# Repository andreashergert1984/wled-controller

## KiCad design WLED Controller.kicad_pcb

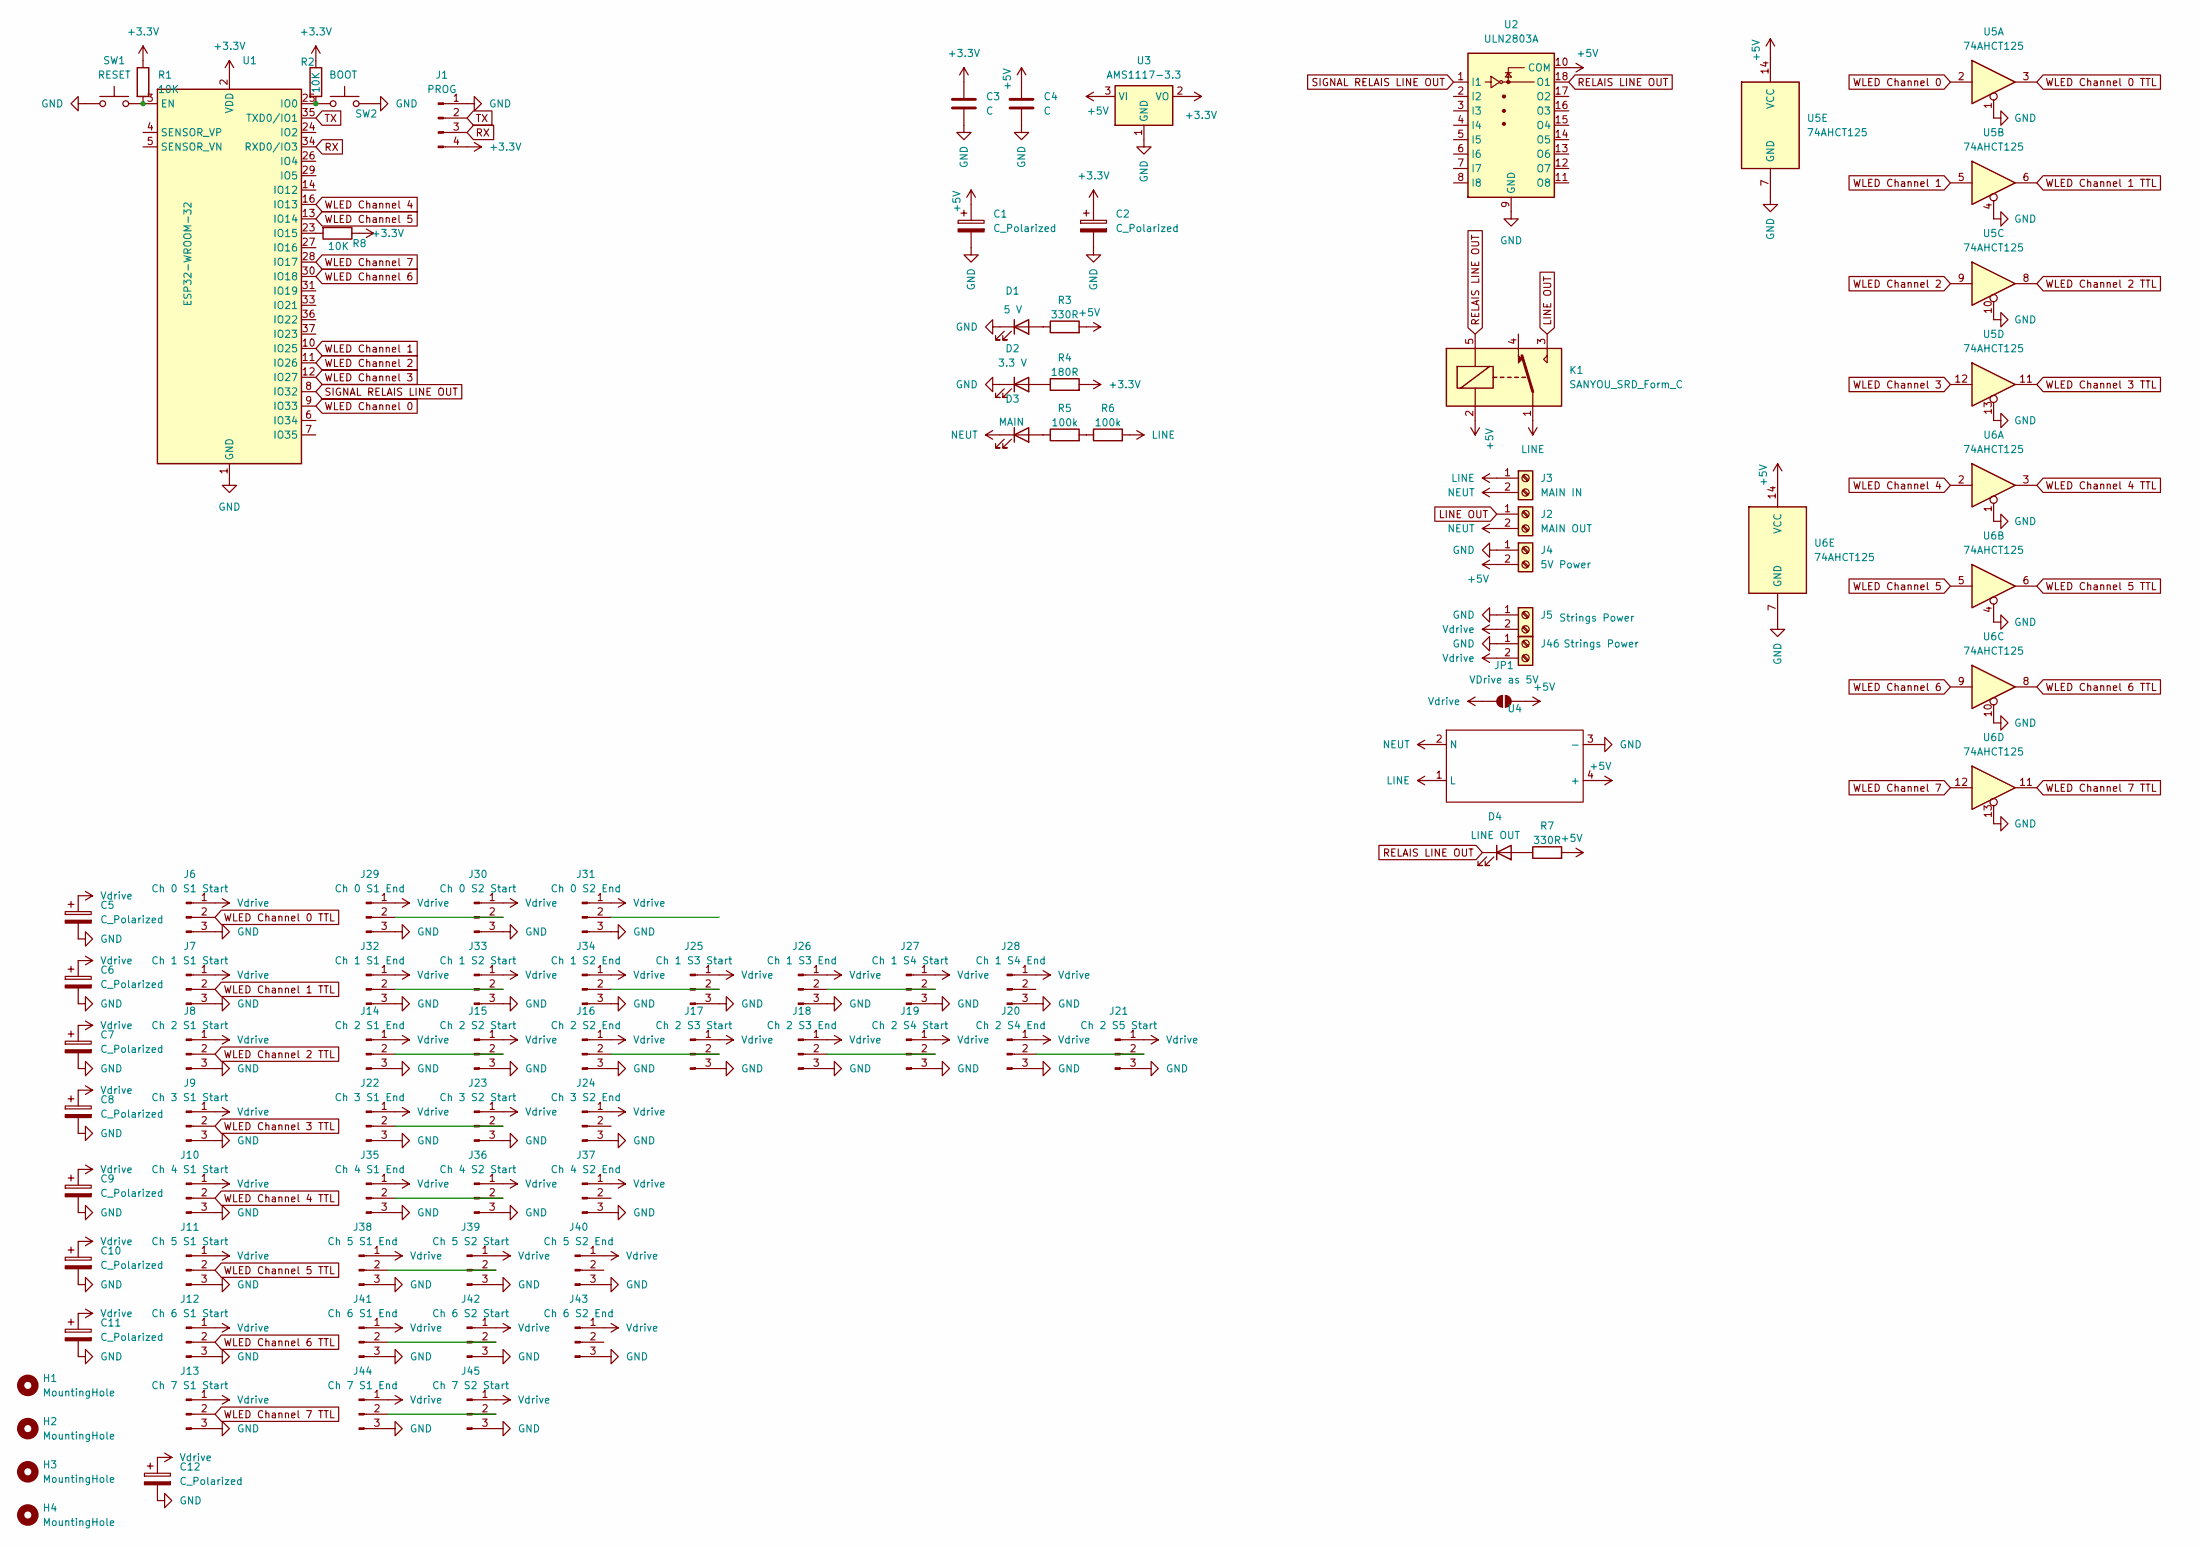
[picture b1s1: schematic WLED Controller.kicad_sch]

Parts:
C1, C2, C5, C6, C7, C8, C9, C10, C11, C12: C_Polarized; CP_Radial_D8.0mm_P3.50mm
C3, C4: C; C_1210_3225Metric_Pad1.33x2.70mm_HandSolder
D1: 5 V; LED_0805_2012Metric_Pad1.15x1.40mm_HandSolder
D2: 3.3 V; LED_0805_2012Metric_Pad1.15x1.40mm_HandSolder
D3: MAIN; LED_0805_2012Metric_Pad1.15x1.40mm_HandSolder
D4: LINE OUT; LED_0805_2012Metric_Pad1.15x1.40mm_HandSolder
H1, H2, H3, H4: MountingHole; MountingHole_3.2mm_M3
J1: PROG; PinHeader_1x04_P2.54mm_Vertical
J2: MAIN OUT; TerminalBlock_bornier-2_P5.08mm
J3: MAIN IN; TerminalBlock_bornier-2_P5.08mm
J4: 5V Power; TerminalBlock_bornier-2_P5.08mm
J5, J46: Strings Power; TerminalBlock_bornier-2_P5.08mm
J6: Ch 0 S1 Start; JST_XH_B3B-XH-AM_1x03_P2.50mm_Vertical
J7: Ch 1 S1 Start; JST_XH_B3B-XH-AM_1x03_P2.50mm_Vertical
J8: Ch 2 S1 Start; JST_XH_B3B-XH-AM_1x03_P2.50mm_Vertical
J9: Ch 3 S1 Start; JST_XH_B3B-XH-AM_1x03_P2.50mm_Vertical
J10: Ch 4 S1 Start; JST_XH_B3B-XH-AM_1x03_P2.50mm_Vertical
J11: Ch 5 S1 Start; JST_XH_B3B-XH-AM_1x03_P2.50mm_Vertical
J12: Ch 6 S1 Start; JST_XH_B3B-XH-AM_1x03_P2.50mm_Vertical
J13: Ch 7 S1 Start; JST_XH_B3B-XH-AM_1x03_P2.50mm_Vertical
J14: Ch 2 S1 End; JST_XH_B3B-XH-AM_1x03_P2.50mm_Vertical
J15: Ch 2 S2 Start; JST_XH_B3B-XH-AM_1x03_P2.50mm_Vertical
J16: Ch 2 S2 End; JST_XH_B3B-XH-AM_1x03_P2.50mm_Vertical
J17: Ch 2 S3 Start; JST_XH_B3B-XH-AM_1x03_P2.50mm_Vertical
J18: Ch 2 S3 End; JST_XH_B3B-XH-AM_1x03_P2.50mm_Vertical
J19: Ch 2 S4 Start; JST_XH_B3B-XH-AM_1x03_P2.50mm_Vertical
J20: Ch 2 S4 End; JST_XH_B3B-XH-AM_1x03_P2.50mm_Vertical
J21: Ch 2 S5 Start; JST_XH_B3B-XH-AM_1x03_P2.50mm_Vertical
J22: Ch 3 S1 End; JST_XH_B3B-XH-AM_1x03_P2.50mm_Vertical
J23: Ch 3 S2 Start; JST_XH_B3B-XH-AM_1x03_P2.50mm_Vertical
J24: Ch 3 S2 End; JST_XH_B3B-XH-AM_1x03_P2.50mm_Vertical
J25: Ch 1 S3 Start; JST_XH_B3B-XH-AM_1x03_P2.50mm_Vertical
J26: Ch 1 S3 End; JST_XH_B3B-XH-AM_1x03_P2.50mm_Vertical
J27: Ch 1 S4 Start; JST_XH_B3B-XH-AM_1x03_P2.50mm_Vertical
J28: Ch 1 S4 End; JST_XH_B3B-XH-AM_1x03_P2.50mm_Vertical
J29: Ch 0 S1 End; JST_XH_B3B-XH-AM_1x03_P2.50mm_Vertical
J30: Ch 0 S2 Start; JST_XH_B3B-XH-AM_1x03_P2.50mm_Vertical
J31: Ch 0 S2 End; JST_XH_B3B-XH-AM_1x03_P2.50mm_Vertical
J32: Ch 1 S1 End; JST_XH_B3B-XH-AM_1x03_P2.50mm_Vertical
J33: Ch 1 S2 Start; JST_XH_B3B-XH-AM_1x03_P2.50mm_Vertical
J34: Ch 1 S2 End; JST_XH_B3B-XH-AM_1x03_P2.50mm_Vertical
J35: Ch 4 S1 End; JST_XH_B3B-XH-AM_1x03_P2.50mm_Vertical
J36: Ch 4 S2 Start; JST_XH_B3B-XH-AM_1x03_P2.50mm_Vertical
J37: Ch 4 S2 End; JST_XH_B3B-XH-AM_1x03_P2.50mm_Vertical
J38: Ch 5 S1 End; JST_XH_B3B-XH-AM_1x03_P2.50mm_Vertical
J39: Ch 5 S2 Start; JST_XH_B3B-XH-AM_1x03_P2.50mm_Vertical
J40: Ch 5 S2 End; JST_XH_B3B-XH-AM_1x03_P2.50mm_Vertical
J41: Ch 6 S1 End; JST_XH_B3B-XH-AM_1x03_P2.50mm_Vertical
J42: Ch 6 S2 Start; JST_XH_B3B-XH-AM_1x03_P2.50mm_Vertical
J43: Ch 6 S2 End; JST_XH_B3B-XH-AM_1x03_P2.50mm_Vertical
J44: Ch 7 S1 End; JST_XH_B3B-XH-AM_1x03_P2.50mm_Vertical
J45: Ch 7 S2 Start; JST_XH_B3B-XH-AM_1x03_P2.50mm_Vertical
JP1: VDrive as 5V; SolderJumper-2_P1.3mm_Open_RoundedPad1.0x1.5mm
K1: SANYOU_SRD_Form_C; Relay_SPDT_SANYOU_SRD_Series_Form_C
R1, R2, R8: 10K; R_0805_2012Metric_Pad1.20x1.40mm_HandSolder
R3, R7: 330R; R_0805_2012Metric_Pad1.20x1.40mm_HandSolder
R4: 180R; R_0805_2012Metric_Pad1.20x1.40mm_HandSolder
R5, R6: 100k; R_0805_2012Metric_Pad1.20x1.40mm_HandSolder
SW1: RESET; SW_Push_SPST_NO_Alps_SKRK
SW2: BOOT; SW_Push_SPST_NO_Alps_SKRK
U1: ESP32-WROOM-32; ESP32-WROOM-32_anh
U2: ULN2803A; SOIC-18W_7.5x11.6mm_P1.27mm
U3: AMS1117-3.3; SOT-223-3_TabPin2
U4: AC-DC-Module12v5v_mall
U5, U6: 74AHCT125; SOIC-14_3.9x8.7mm_P1.27mm

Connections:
+3.3V: C2.1, C3.2, J1.4, R1.1, R2.1, R4.2, R8.1, U1.2 (VDD), U3.2 (VO)
+5V: C1.1, C4.2, J4.2, JP1.2 (B), K1.2, R3.2, R7.2, U2.10 (COM), U3.3 (VI), U4.4 (+), U5.14 (VCC), U6.14 (VCC)
GND: C1.2, C2.2, C3.1, C4.1, C5.2, C6.2, C7.2, C8.2, C9.2, C10.2, C11.2, C12.2, D1.1 (K), D2.1 (K), J1.1, J4.1, J5.1, J6.3, J7.3, J8.3, J9.3, J10.3, J11.3, J12.3, J13.3, J14.3, J15.3, J16.3, J17.3, J18.3, J19.3, J20.3, J21.3, J22.3, J23.3, J24.3, J25.3, J26.3, J27.3, J28.3, J29.3, J30.3, J31.3, J32.3, J33.3, J34.3, J35.3, J36.3, J37.3, J38.3, J39.3, J40.3, J41.3, J42.3, J43.3, J44.3, J45.3, J46.1, SW1.1, SW2.2, U1.1 (GND), U1.15 (GND), U1.38 (GND), U1.39 (GND), U2.9 (GND), U3.1 (GND), U4.3 (-), U5.1, U5.4, U5.7 (GND), U5.10, U5.13, U6.1, U6.4, U6.7 (GND), U6.10, U6.13
LINE: J3.1, K1.1, R6.2, U4.1 (L)
LINE OUT: J2.1, K1.3
NEUT: D3.1 (K), J2.2, J3.2, U4.2 (N)
unnamed: D1.2 (A), R3.1
unnamed: D2.2 (A), R4.1
unnamed: D3.2 (A), R5.1
unnamed: D4.2 (A), R7.1
unnamed: J14.2, J15.2
unnamed: J16.2, J17.2
unnamed: J18.2, J19.2
unnamed: J20.2, J21.2
unnamed: J22.2, J23.2
unnamed: J25.2, J34.2
unnamed: J26.2, J27.2
unnamed: J29.2, J30.2
unnamed: J32.2, J33.2
unnamed: J35.2, J36.2
unnamed: J38.2, J39.2
unnamed: J41.2, J42.2
unnamed: J44.2, J45.2
unnamed: R5.2, R6.1
unnamed: R1.2, SW1.2, U1.3 (EN)
unnamed: R2.2, SW2.1, U1.25 (IO0)
unnamed: R8.2, U1.23 (IO15)
RELAIS LINE OUT: D4.1 (K), K1.5, U2.18 (O1)
RX: J1.3, U1.34 (RXD0/IO3)
SIGNAL RELAIS LINE OUT: U1.8 (IO32), U2.1 (I1)
TX: J1.2, U1.35 (TXD0/IO1)
Vdrive: C5.1, C6.1, C7.1, C8.1, C9.1, C10.1, C11.1, C12.1, J5.2, J6.1, J7.1, J8.1, J9.1, J10.1, J11.1, J12.1, J13.1, J14.1, J15.1, J16.1, J17.1, J18.1, J19.1, J20.1, J21.1, J22.1, J23.1, J24.1, J25.1, J26.1, J27.1, J28.1, J29.1, J30.1, J31.1, J32.1, J33.1, J34.1, J35.1, J36.1, J37.1, J38.1, J39.1, J40.1, J41.1, J42.1, J43.1, J44.1, J45.1, J46.2, JP1.1 (A)
WLED Channel 0: U1.9 (IO33), U5.2
WLED Channel 0 TTL: J6.2, U5.3
WLED Channel 1: U1.10 (IO25), U5.5
WLED Channel 1 TTL: J7.2, U5.6
WLED Channel 2: U1.11 (IO26), U5.9
WLED Channel 2 TTL: J8.2, U5.8
WLED Channel 3: U1.12 (IO27), U5.12
WLED Channel 3 TTL: J9.2, U5.11
WLED Channel 4: U1.16 (IO13), U6.2
WLED Channel 4 TTL: J10.2, U6.3
WLED Channel 5: U1.13 (IO14), U6.5
WLED Channel 5 TTL: J11.2, U6.6
WLED Channel 6: U1.30 (IO18), U6.9
WLED Channel 6 TTL: J12.2, U6.8
WLED Channel 7: U1.28 (IO17), U6.12
WLED Channel 7 TTL: J13.2, U6.11

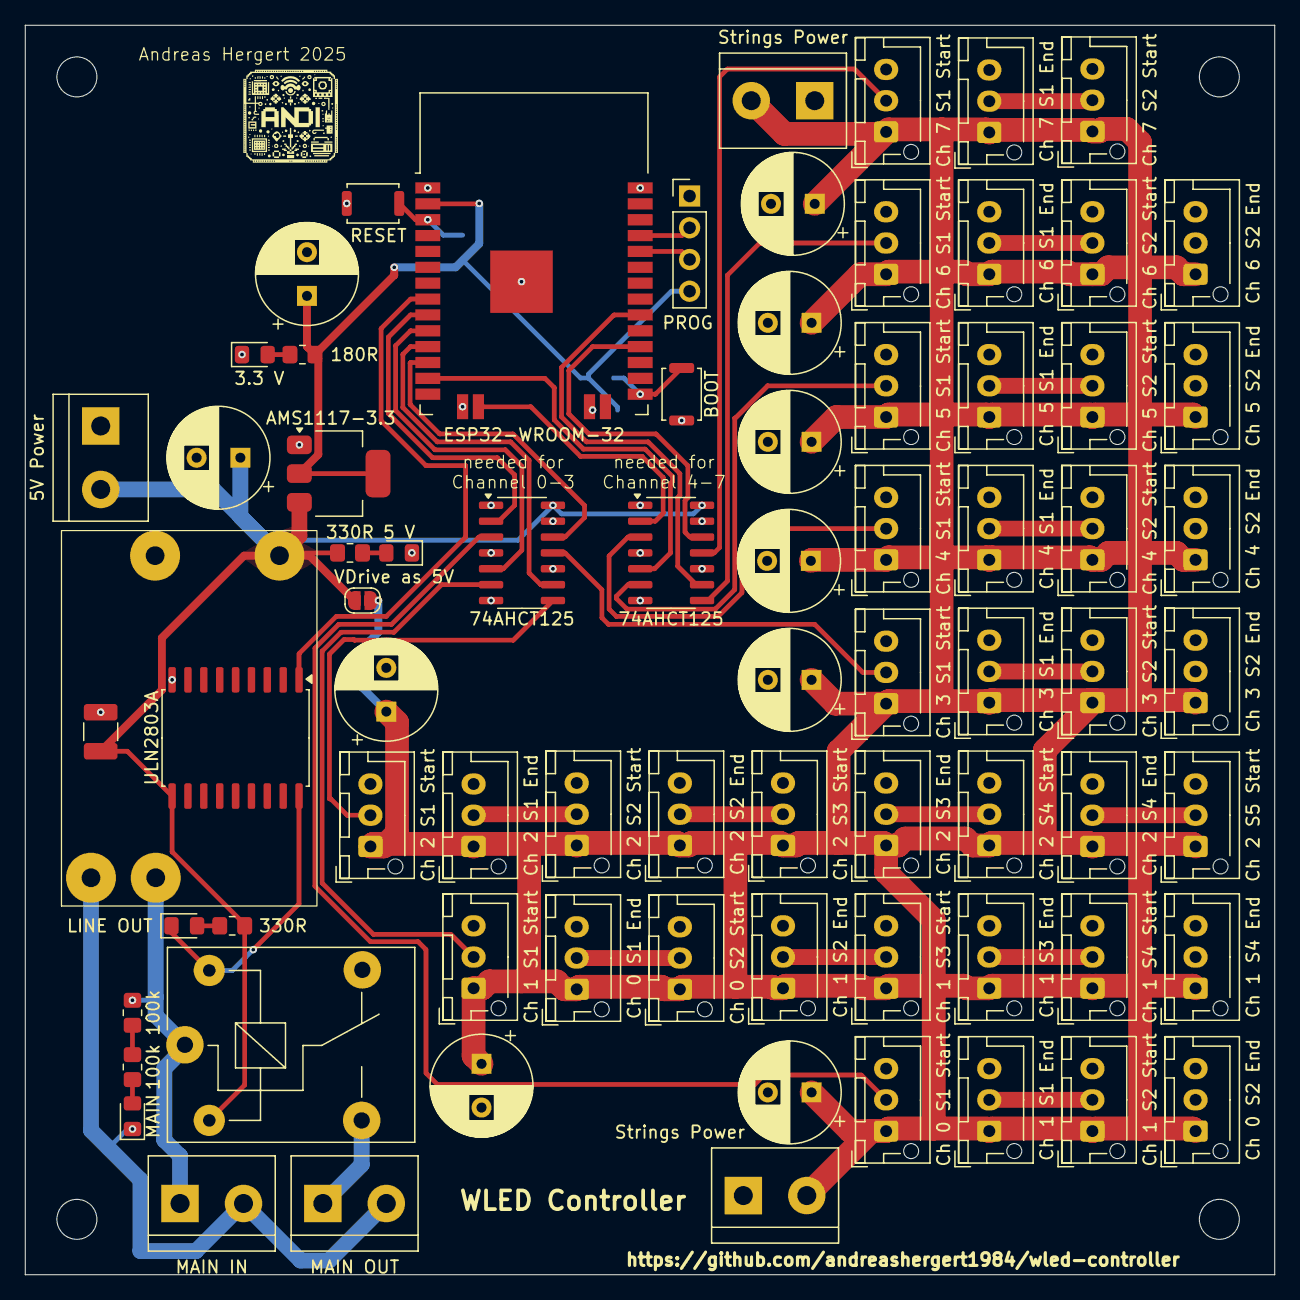
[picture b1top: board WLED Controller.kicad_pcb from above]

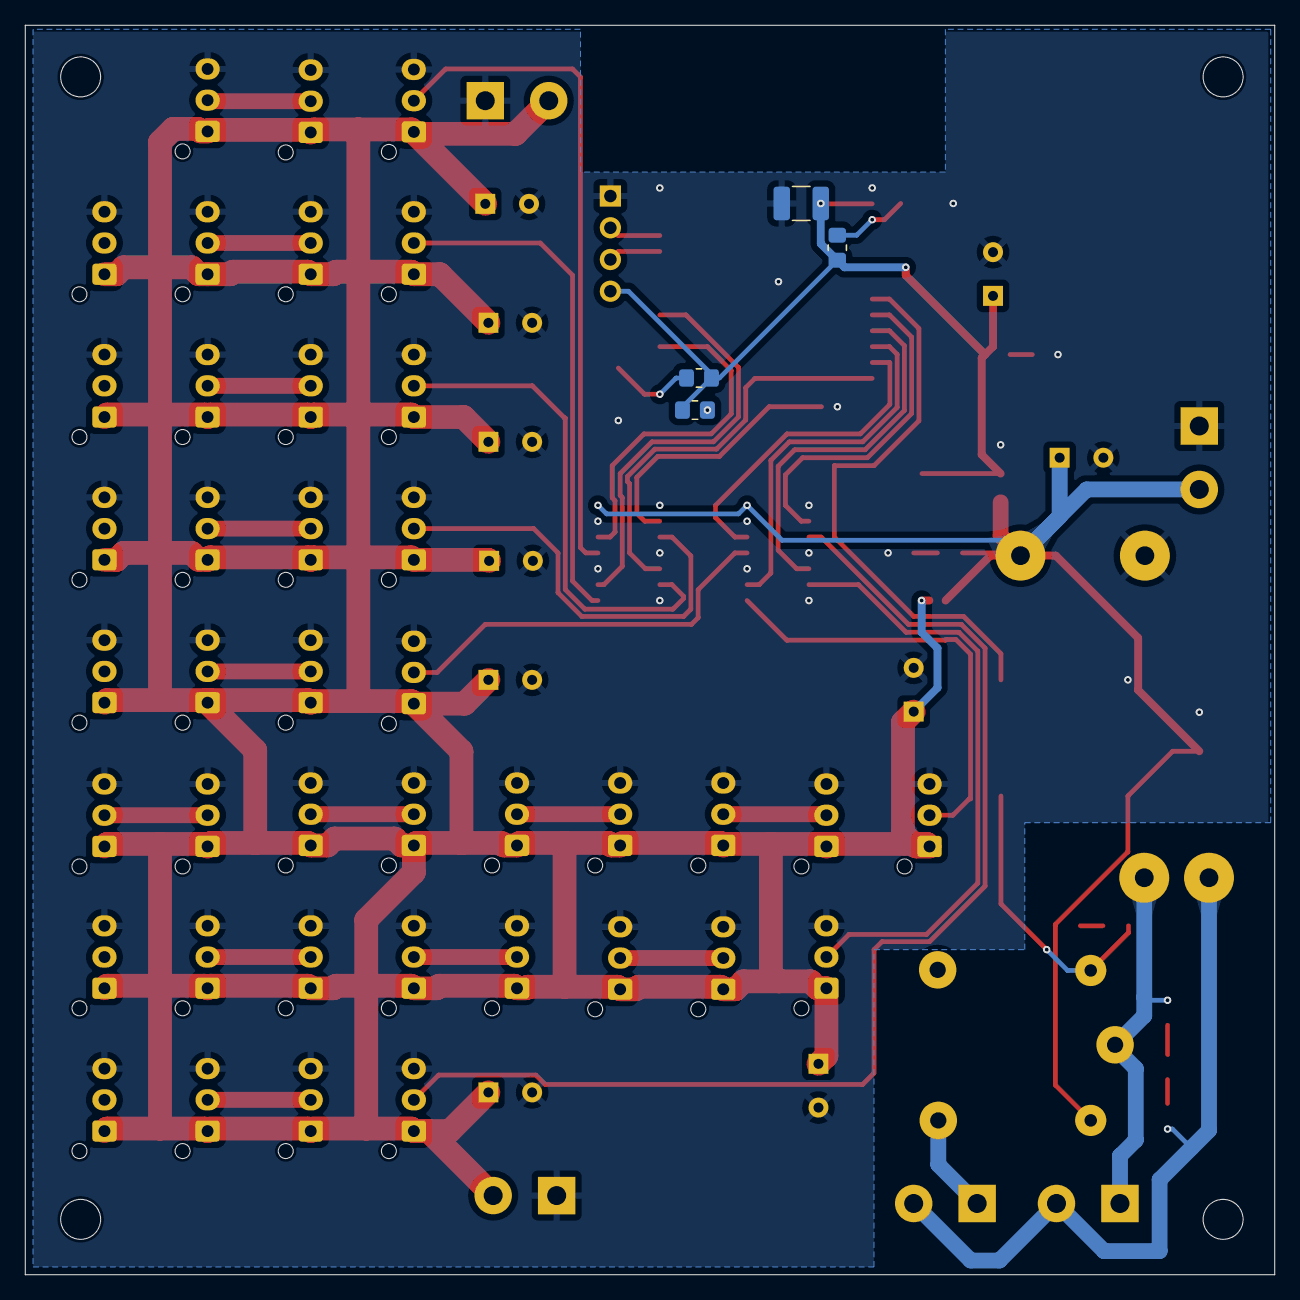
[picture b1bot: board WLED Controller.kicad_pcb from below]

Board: 2 copper layers, 100.0 x 100.0 mm, 84 parts (4 on the bottom side), 48 nets.

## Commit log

2025-02-25 initial version
2025-02-25 added github url
2025-02-25 added production exports
